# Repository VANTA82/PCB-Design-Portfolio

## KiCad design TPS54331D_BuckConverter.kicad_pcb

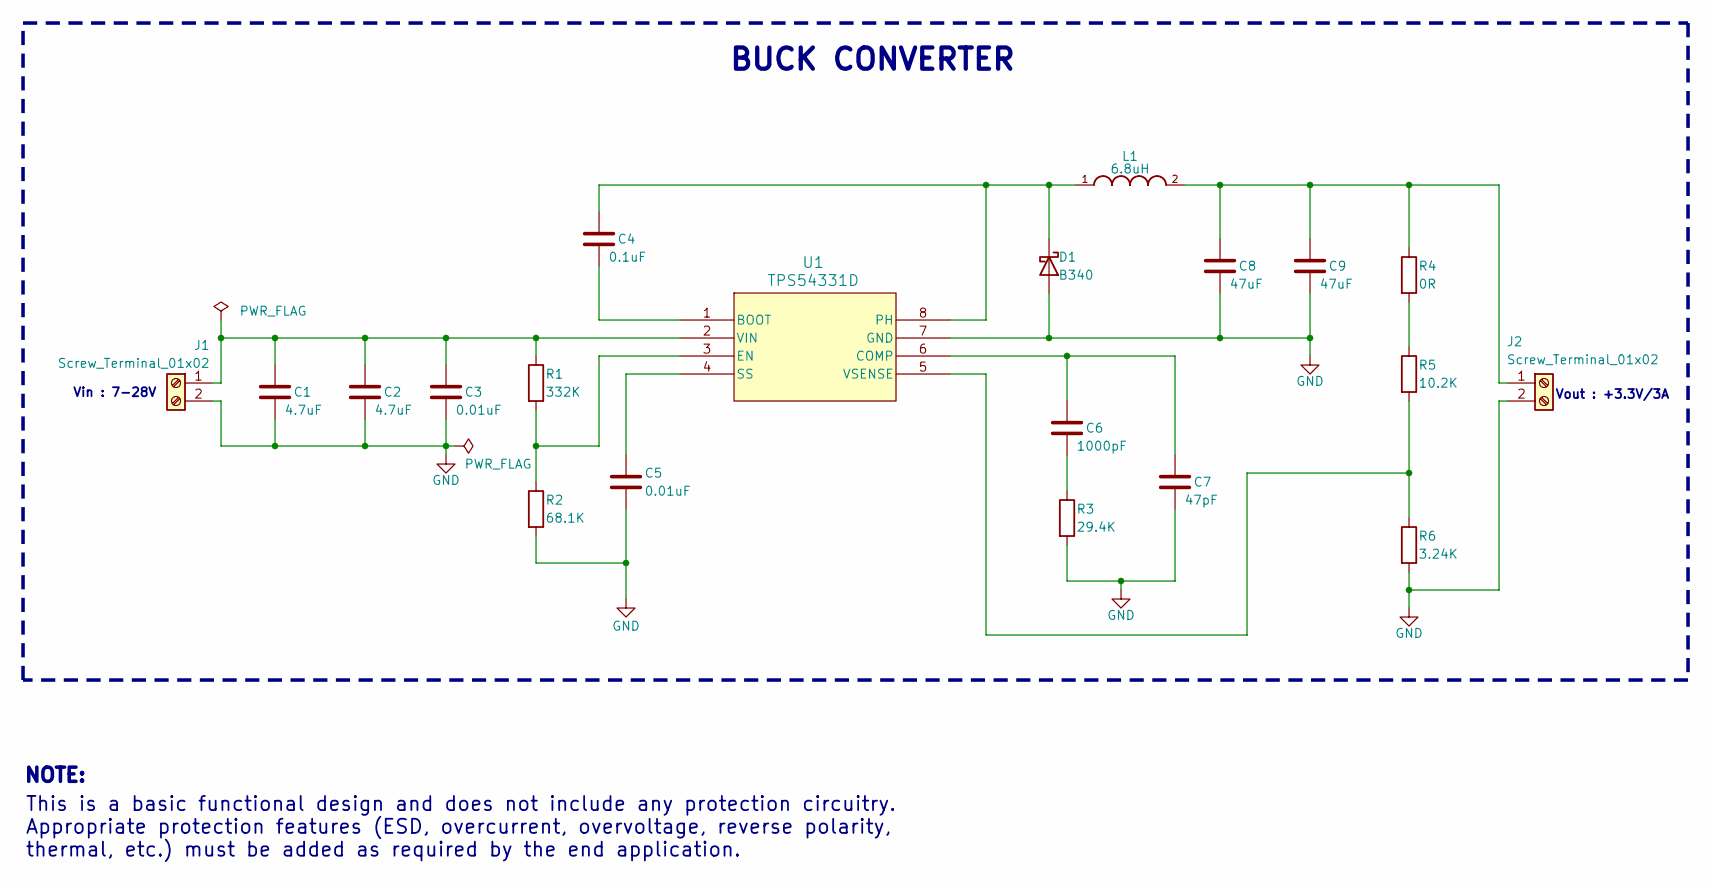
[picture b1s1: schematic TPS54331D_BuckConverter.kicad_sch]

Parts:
C1, C2: 4.7uF; C_0805_2012Metric
C3, C5: 0.01uF; C_0805_2012Metric
C4: 0.1uF; C_0805_2012Metric
C6: 1000pF; C_0805_2012Metric
C7: 47pF; C_0805_2012Metric
C8, C9: 47uF; C_0805_2012Metric
D1: B340; D_SMA
J1, J2: Screw_Terminal_01x02; TerminalBlock_Phoenix_MPT-0,5-2-2.54_1x02_P2.54mm_Horizontal
L1: 6.8uH; L_Bourns-SRN8040_8x8.15mm
R1: 332K; R_0805_2012Metric
R2: 68.1K; R_0805_2012Metric
R3: 29.4K; R_0805_2012Metric
R4: 0R; R_0805_2012Metric
R5: 10.2K; R_0805_2012Metric
R6: 3.24K; R_0805_2012Metric
U1: TPS54331D; SOIC-8_5.23x5.23mm_P1.27mm

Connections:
GND: C1.2, C2.2, C3.2, C5.2, C7.2, C8.2, C9.2, D1.2 (A), J1.2, J2.2, R2.2, R3.2, R6.2, U1.7 (GND)
unnamed: C6.2, R3.1
unnamed: C4.1, D1.1 (K), L1.1, U1.8 (PH)
unnamed: C1.1, C2.1, C3.1, J1.1, R1.1, U1.2 (VIN)
unnamed: C8.1, C9.1, J2.1, L1.2, R4.1
unnamed: R4.2, R5.1
unnamed: C4.2, U1.1 (BOOT)
unnamed: C6.1, C7.1, U1.6 (COMP)
unnamed: R1.2, R2.1, U1.3 (EN)
unnamed: C5.1, U1.4 (SS)
unnamed: R5.2, R6.1, U1.5 (VSENSE)

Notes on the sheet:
Vout : +3.3V/3A
Vin : 7-28V
BUCK CONVERTER
NOTE:
This is a basic functional design and does not include any protection circuitry. Appropriate protection features (ESD, overcurrent, overvoltage, reverse polarity, thermal, etc.) must be added as required by the end application.

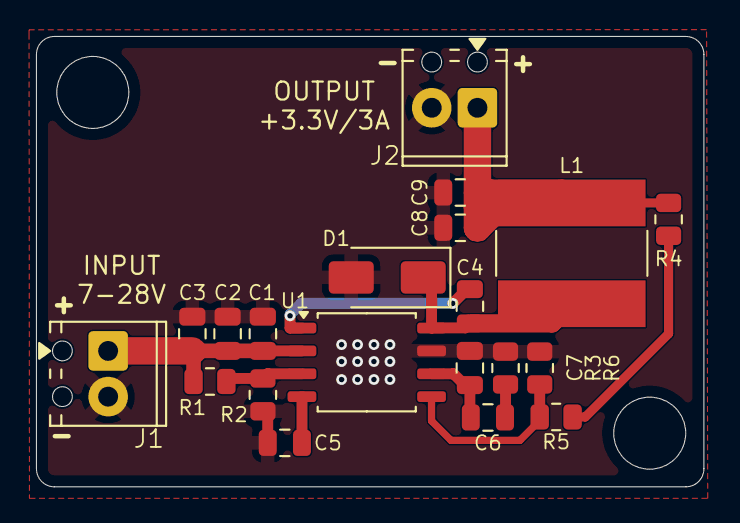
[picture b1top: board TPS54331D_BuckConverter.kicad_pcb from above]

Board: 2 copper layers, 37.1 x 25.0 mm, 20 parts (0 on the bottom side), 11 nets.
